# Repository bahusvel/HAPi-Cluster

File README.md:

# ClusterPipe
Flow processing scheduler daemon for real time parallel stream processing

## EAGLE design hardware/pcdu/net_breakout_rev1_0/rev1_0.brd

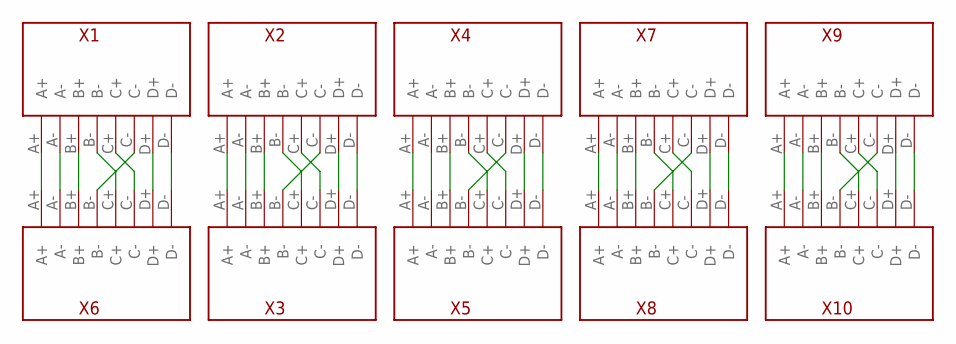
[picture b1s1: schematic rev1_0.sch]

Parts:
X1, X2, X3, X4, X5, X6, X7, X8, X9, X10: ETHER_BRKOUT

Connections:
unnamed: X1.A+, X6.A+
unnamed: X1.A-, X6.A-
unnamed: X1.B+, X6.B+
unnamed: X1.C-, X6.B-
unnamed: X1.B-, X6.C+
unnamed: X1.C+, X6.C-
unnamed: X1.D+, X6.D+
unnamed: X1.D-, X6.D-
unnamed: X2.A+, X3.A+
unnamed: X2.A-, X3.A-
unnamed: X2.B+, X3.B+
unnamed: X2.C-, X3.B-
unnamed: X2.B-, X3.C+
unnamed: X2.C+, X3.C-
unnamed: X2.D+, X3.D+
unnamed: X2.D-, X3.D-
unnamed: X4.A+, X5.A+
unnamed: X4.A-, X5.A-
unnamed: X4.B+, X5.B+
unnamed: X4.C-, X5.B-
unnamed: X4.B-, X5.C+
unnamed: X4.C+, X5.C-
unnamed: X4.D+, X5.D+
unnamed: X4.D-, X5.D-
unnamed: X7.A+, X8.A+
unnamed: X7.A-, X8.A-
unnamed: X7.B+, X8.B+
unnamed: X7.C-, X8.B-
unnamed: X7.B-, X8.C+
unnamed: X7.C+, X8.C-
unnamed: X7.D+, X8.D+
unnamed: X7.D-, X8.D-
unnamed: X9.A+, X10.A+
unnamed: X9.A-, X10.A-
unnamed: X9.B+, X10.B+
unnamed: X9.C-, X10.B-
unnamed: X9.B-, X10.C+
unnamed: X9.C+, X10.C-
unnamed: X9.D+, X10.D+
unnamed: X9.D-, X10.D-

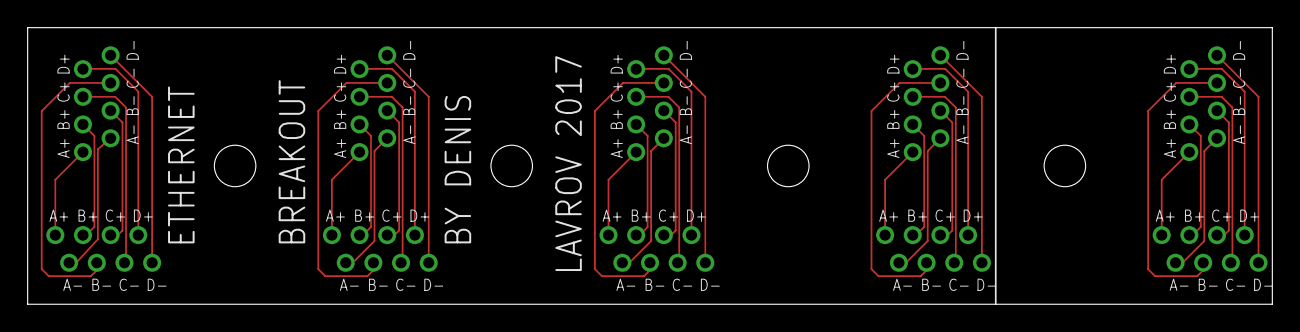
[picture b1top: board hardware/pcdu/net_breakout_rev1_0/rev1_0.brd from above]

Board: 2 copper layers, 90.0 x 20.0 mm, 10 parts (0 on the bottom side), 40 nets.

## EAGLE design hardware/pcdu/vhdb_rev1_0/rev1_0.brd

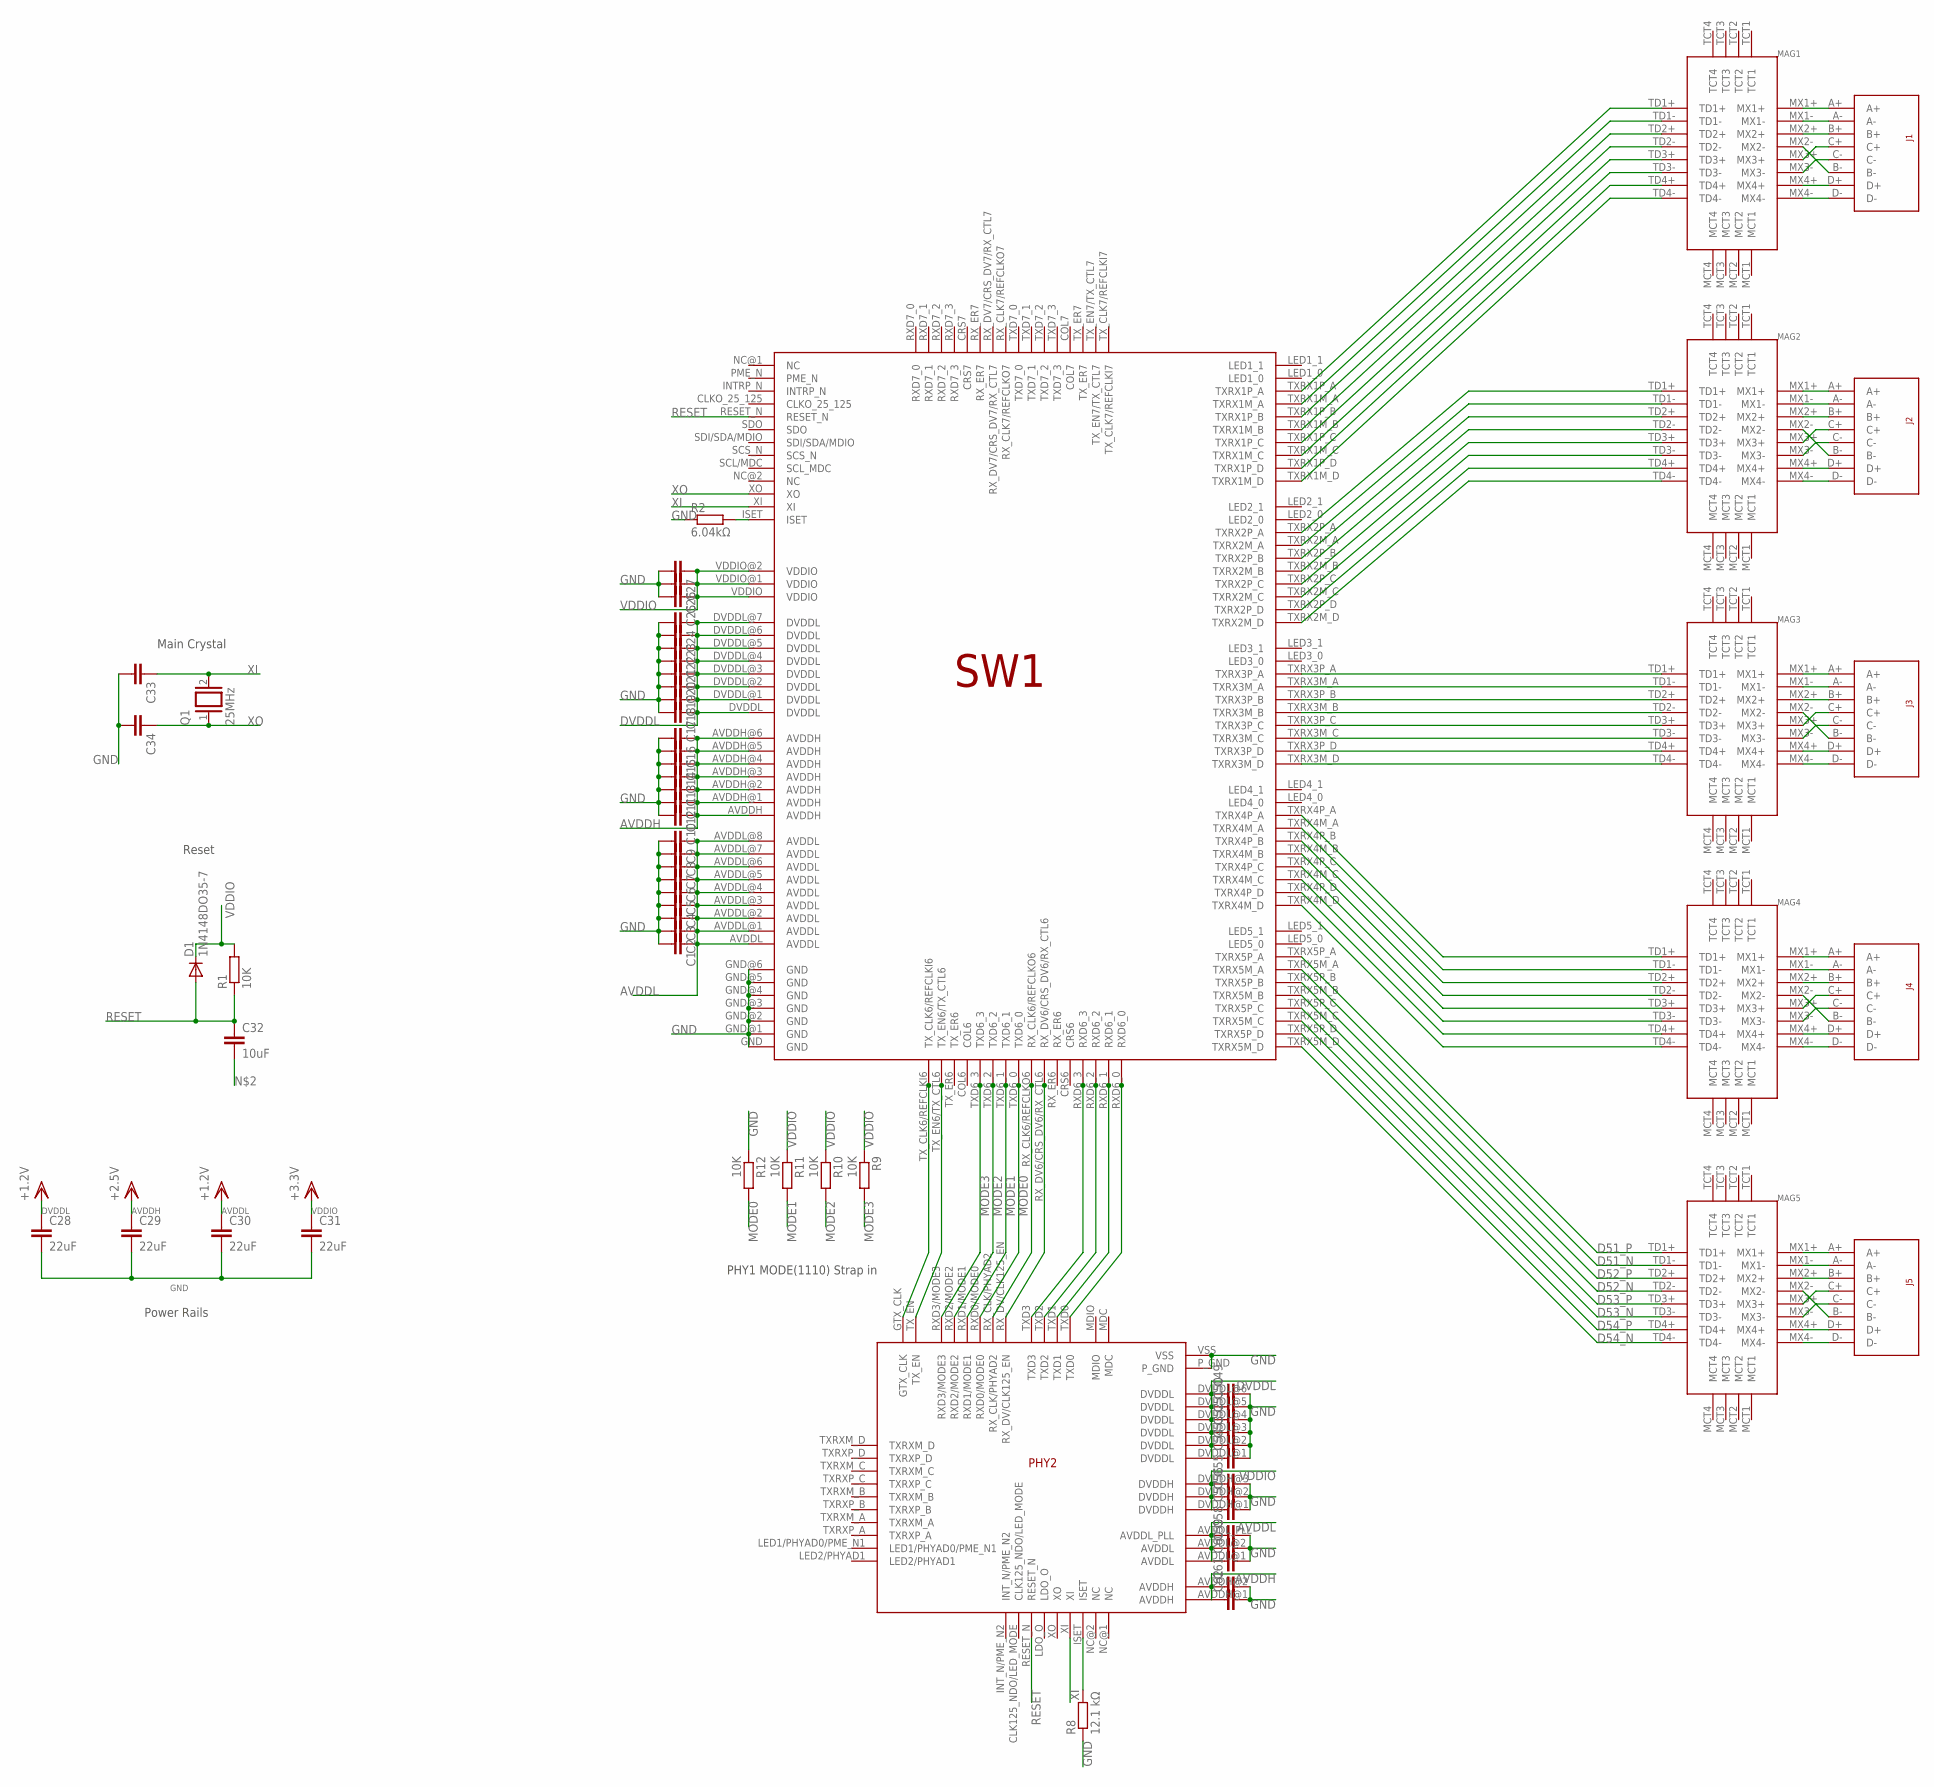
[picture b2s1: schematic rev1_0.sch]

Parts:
C1, C2, C3, C4, C5, C6, C7, C8, C9, C10, C11, C12, C13, C14, C15, C16, C17, C18, C19, C20, C21, C22, C23, C24, C25, C26, C27, C33, C34, C49, C50, C51, C52, C53, C54, C55, C56, C57, C58, C59, C60, C61, C62: C-EUC0805; C0805
C28, C29, C30, C31: 22uF; C0805
C32: 10uF; C0805
D1: 1N4148DO35-7; DO35-7
J1, J2, J3, J4, J5: AJP92A8813
MAG1, MAG2, MAG3, MAG4, MAG5: 749020010A; 749023010A
PHY2: KSZ9031RNX
Q1: 25MHz; QS
R1, R9, R10, R11, R12: 10K; R0805
R2: 6.04kΩ; R0805
R8: 12.1 kΩ; R0805
SW1: KSZ9897RTXC

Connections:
AVDDH: C10.1, C11.1, C12.1, C13.1, C14.1, C15.1, C16.1, C29.1, PHY2.AVDDH@1 (AVDDH), PHY2.AVDDH@2 (AVDDH), SW1.AVDDH, SW1.AVDDH@1 (AVDDH), SW1.AVDDH@2 (AVDDH), SW1.AVDDH@3 (AVDDH), SW1.AVDDH@4 (AVDDH), SW1.AVDDH@5 (AVDDH), SW1.AVDDH@6 (AVDDH)
AVDDL: C1.1, C2.1, C3.1, C4.1, C5.1, C6.1, C7.1, C8.1, C9.1, C30.1, PHY2.AVDDL@1 (AVDDL), PHY2.AVDDL@2 (AVDDL), PHY2.AVDDL_PLL, SW1.AVDDL, SW1.AVDDL@1 (AVDDL), SW1.AVDDL@2 (AVDDL), SW1.AVDDL@3 (AVDDL), SW1.AVDDL@4 (AVDDL), SW1.AVDDL@5 (AVDDL), SW1.AVDDL@6 (AVDDL), SW1.AVDDL@7 (AVDDL), SW1.AVDDL@8 (AVDDL)
D51_N: MAG5.TD1-, SW1.TXRX5M_A
D51_P: MAG5.TD1+, SW1.TXRX5P_A
D52_N: MAG5.TD2-, SW1.TXRX5M_B
D52_P: MAG5.TD2+, SW1.TXRX5P_B
D53_N: MAG5.TD3-, SW1.TXRX5M_C
D53_P: MAG5.TD3+, SW1.TXRX5P_C
D54_N: MAG5.TD4-, SW1.TXRX5M_D
D54_P: MAG5.TD4+, SW1.TXRX5P_D
DVDDL: C17.1, C24.1, C28.1, C49.1, PHY2.DVDDL@1 (DVDDL), PHY2.DVDDL@2 (DVDDL), PHY2.DVDDL@3 (DVDDL), PHY2.DVDDL@4 (DVDDL), PHY2.DVDDL@5 (DVDDL), PHY2.DVDDL@6 (DVDDL), SW1.DVDDL, SW1.DVDDL@1 (DVDDL), SW1.DVDDL@2 (DVDDL), SW1.DVDDL@3 (DVDDL), SW1.DVDDL@4 (DVDDL), SW1.DVDDL@5 (DVDDL), SW1.DVDDL@6 (DVDDL), SW1.DVDDL@7 (DVDDL)
GND: C1.2, C2.2, C3.2, C4.2, C5.2, C6.2, C7.2, C8.2, C9.2, C10.2, C11.2, C12.2, C13.2, C14.2, C15.2, C16.2, C17.2, C18.2, C19.2, C20.2, C21.2, C22.2, C23.2, C24.2, C25.2, C26.2, C27.2, C28.2, C29.2, C30.2, C31.2, C33.2, C34.2, C49.2, C51.2, C52.2, C53.2, C54.2, C55.2, C57.2, C58.2, C60.2, C61.2, C62.2, PHY2.P_GND, PHY2.VSS, R2.1, R8.1, R12.1, SW1.GND, SW1.GND@1 (GND), SW1.GND@2 (GND), SW1.GND@3 (GND), SW1.GND@4 (GND), SW1.GND@5 (GND), SW1.GND@6 (GND)
MODE0: PHY2.RXD0/MODE0, R12.2, SW1.TXD6_0
MODE1: PHY2.RXD1/MODE1, R11.2, SW1.TXD6_1
MODE2: PHY2.RXD2/MODE2, R10.2, SW1.TXD6_2
MODE3: PHY2.RXD3/MODE3, R9.2, SW1.TXD6_3
unnamed: MAG1.TD1+, SW1.TXRX1P_A
unnamed: MAG1.TD1-, SW1.TXRX1M_A
unnamed: MAG1.TD2+, SW1.TXRX1P_B
unnamed: MAG1.TD2-, SW1.TXRX1M_B
unnamed: R2.2, SW1.ISET
unnamed: MAG1.TD3+, SW1.TXRX1P_C
unnamed: MAG1.TD3-, SW1.TXRX1M_C
unnamed: MAG1.TD4+, SW1.TXRX1P_D
unnamed: MAG1.TD4-, SW1.TXRX1M_D
unnamed: MAG2.TD1+, SW1.TXRX2P_A
unnamed: MAG2.TD1-, SW1.TXRX2M_A
unnamed: MAG2.TD2+, SW1.TXRX2P_B
unnamed: MAG2.TD2-, SW1.TXRX2M_B
unnamed: MAG2.TD3+, SW1.TXRX2P_C
unnamed: MAG2.TD3-, SW1.TXRX2M_C
unnamed: MAG2.TD4+, SW1.TXRX2P_D
unnamed: MAG2.TD4-, SW1.TXRX2M_D
unnamed: MAG3.TD1+, SW1.TXRX3P_A
unnamed: MAG3.TD1-, SW1.TXRX3M_A
unnamed: MAG3.TD2+, SW1.TXRX3P_B
unnamed: MAG3.TD2-, SW1.TXRX3M_B
unnamed: MAG3.TD3+, SW1.TXRX3P_C
unnamed: MAG3.TD3-, SW1.TXRX3M_C
unnamed: MAG3.TD4+, SW1.TXRX3P_D
unnamed: MAG3.TD4-, SW1.TXRX3M_D
unnamed: MAG4.TD4-, SW1.TXRX4M_D
unnamed: MAG4.TD4+, SW1.TXRX4P_D
unnamed: MAG4.TD3-, SW1.TXRX4M_C
unnamed: MAG4.TD3+, SW1.TXRX4P_C
unnamed: MAG4.TD2-, SW1.TXRX4M_B
unnamed: MAG4.TD2+, SW1.TXRX4P_B
unnamed: MAG4.TD1-, SW1.TXRX4M_A
unnamed: MAG4.TD1+, SW1.TXRX4P_A
unnamed: J1.A+, MAG1.MX1+
unnamed: J1.A-, MAG1.MX1-
unnamed: J1.B+, MAG1.MX2+
unnamed: J1.B-, MAG1.MX2-
unnamed: J1.C+, MAG1.MX3+
unnamed: J1.C-, MAG1.MX3-
unnamed: J1.D+, MAG1.MX4+
unnamed: J1.D-, MAG1.MX4-
unnamed: J2.A+, MAG2.MX1+
unnamed: J2.A-, MAG2.MX1-
unnamed: J2.B+, MAG2.MX2+
unnamed: J2.B-, MAG2.MX2-
unnamed: J2.C+, MAG2.MX3+
unnamed: J2.C-, MAG2.MX3-
unnamed: J2.D+, MAG2.MX4+
unnamed: J2.D-, MAG2.MX4-
unnamed: J3.A+, MAG3.MX1+
unnamed: J3.A-, MAG3.MX1-
unnamed: J3.B+, MAG3.MX2+
unnamed: J3.B-, MAG3.MX2-
unnamed: J3.C+, MAG3.MX3+
unnamed: J3.C-, MAG3.MX3-
unnamed: J3.D+, MAG3.MX4+
unnamed: J3.D-, MAG3.MX4-
unnamed: J4.A+, MAG4.MX1+
unnamed: J4.A-, MAG4.MX1-
unnamed: J4.B+, MAG4.MX2+
unnamed: J4.B-, MAG4.MX2-
unnamed: J4.C+, MAG4.MX3+
unnamed: J4.C-, MAG4.MX3-
unnamed: J4.D+, MAG4.MX4+
unnamed: J4.D-, MAG4.MX4-
unnamed: J5.A+, MAG5.MX1+
unnamed: J5.A-, MAG5.MX1-
unnamed: J5.B+, MAG5.MX2+
unnamed: J5.B-, MAG5.MX2-
unnamed: J5.C+, MAG5.MX3+
unnamed: J5.C-, MAG5.MX3-
unnamed: J5.D+, MAG5.MX4+
unnamed: J5.D-, MAG5.MX4-
unnamed: PHY2.TXD0, SW1.RXD6_0
unnamed: PHY2.TXD1, SW1.RXD6_1
unnamed: PHY2.TXD2, SW1.RXD6_2
unnamed: PHY2.TXD3, SW1.RXD6_3
unnamed: PHY2.RX_DV/CLK125_EN, SW1.RX_DV6/CRS_DV6/RX_C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
unnamed: PHY2.RX_CLK/PHYAD2, SW1.RX_CLK6/REFCLKO6
unnamed: PHY2.TX_EN, SW1.TX_EN6/TX_CTL6
unnamed: PHY2.GTX_CLK, SW1.TX_CLK6/REFCLKI6
unnamed: PHY2.ISET, R8.2
RESET: C32.1, D1.A, PHY2.RESET_N, R1.1, SW1.RESET_N
VDDIO: C25.1, C26.1, C27.1, C31.1, D1.C, PHY2.DVDDH@1 (DVDDH), PHY2.DVDDH@2 (DVDDH), PHY2.DVDDH@3 (DVDDH), R1.2, R9.1, R10.1, R11.1, SW1.VDDIO, SW1.VDDIO@1 (VDDIO), SW1.VDDIO@2 (VDDIO)
XI: C33.1, PHY2.XI, Q1.2, SW1.XI
XO: C34.1, Q1.1, SW1.XO

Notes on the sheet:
Main Crystal
Reset
Power Rails
PHY1 MODE(1110) Strap in

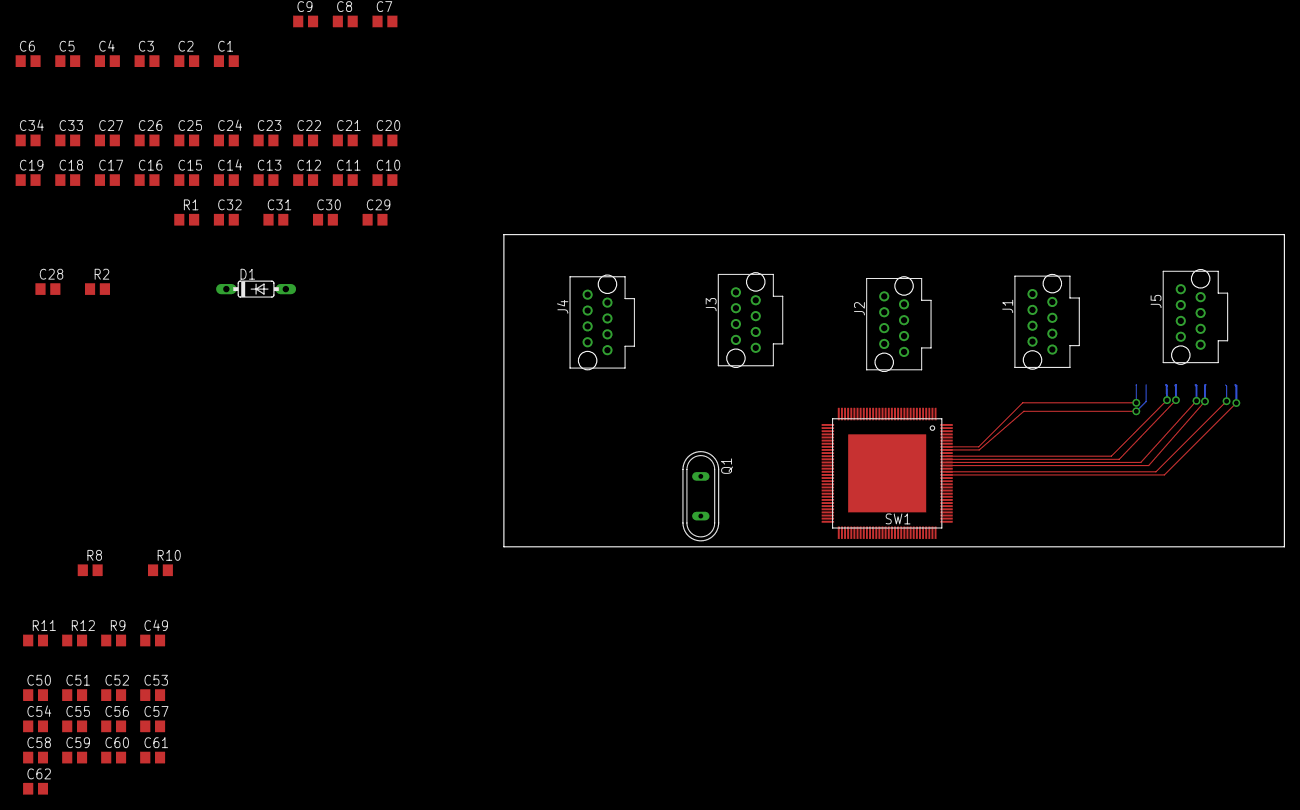
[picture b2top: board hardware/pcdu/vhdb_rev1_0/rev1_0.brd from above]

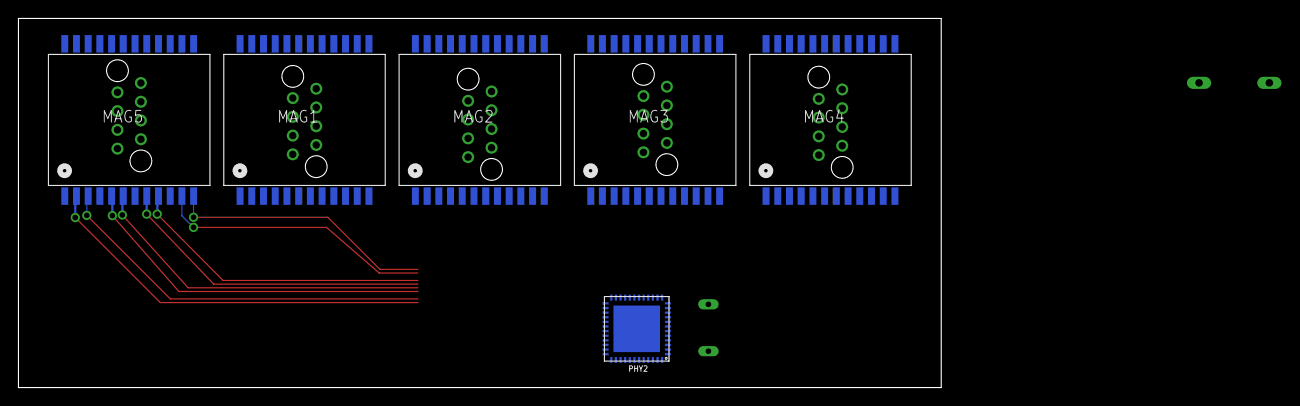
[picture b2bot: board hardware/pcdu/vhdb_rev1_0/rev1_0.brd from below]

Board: 2 copper layers, 100.0 x 40.0 mm, 69 parts (6 on the bottom side), 102 nets.

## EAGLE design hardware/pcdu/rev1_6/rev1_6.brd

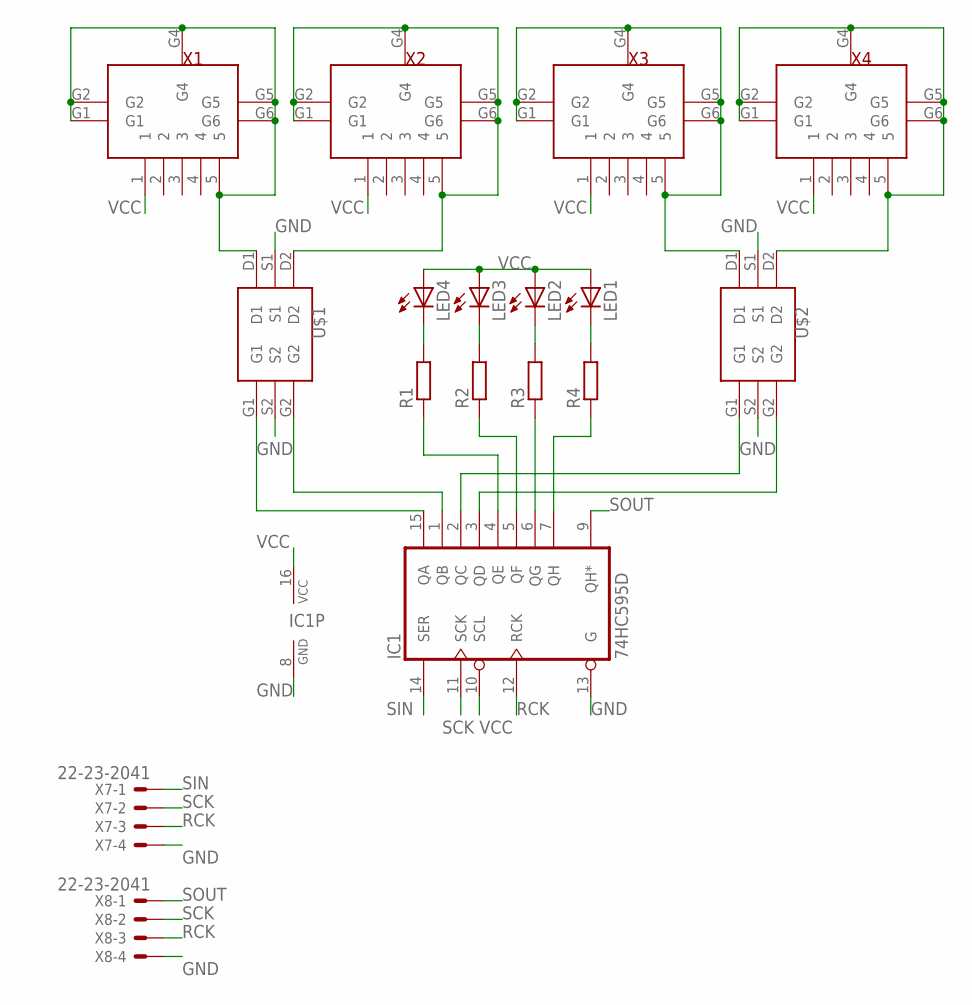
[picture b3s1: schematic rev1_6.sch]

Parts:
IC1: 74HC595D; SO16
LED1, LED2, LED3, LED4: LED_E; LED_1206
R1, R2, R3, R4: RR1005; R1005
U$1, U$2: FDC6305N; FDC6305
X1, X2, X3, X4: MUSBV
X7, X8: 22-23-2041

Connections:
GND: IC1.8 (GND), IC1.13 (G), U$1.S1, U$1.S2, U$2.S1, U$2.S2, X7.4, X8.4
unnamed: IC1.15 (QA), U$1.G1
unnamed: IC1.1 (QB), U$1.G2
unnamed: IC1.2 (QC), U$2.G1
unnamed: IC1.3 (QD), U$2.G2
unnamed: LED4.C, R1.2
unnamed: LED3.C, R2.2
unnamed: LED2.C, R3.2
unnamed: LED1.C, R4.2
unnamed: U$1.D1, X1.5, X1.G1, X1.G2, X1.G4, X1.G5, X1.G6
unnamed: U$1.D2, X2.5, X2.G1, X2.G2, X2.G4, X2.G5, X2.G6
unnamed: U$2.D1, X3.5, X3.G1, X3.G2, X3.G4, X3.G5, X3.G6
unnamed: U$2.D2, X4.5, X4.G1, X4.G2, X4.G4, X4.G5, X4.G6
unnamed: IC1.4 (QE), R1.1
unnamed: IC1.5 (QF), R2.1
unnamed: IC1.6 (QG), R3.1
unnamed: IC1.7 (QH), R4.1
RCK: IC1.12 (RCK), X7.3, X8.3
SCK: IC1.11 (SCK), X7.2, X8.2
SIN: IC1.14 (SER), X7.1
SOUT: IC1.9 (QH*), X8.1
VCC: IC1.10 (SCL), IC1.16 (VCC), LED1.A, LED2.A, LED3.A, LED4.A, X1.1, X2.1, X3.1, X4.1

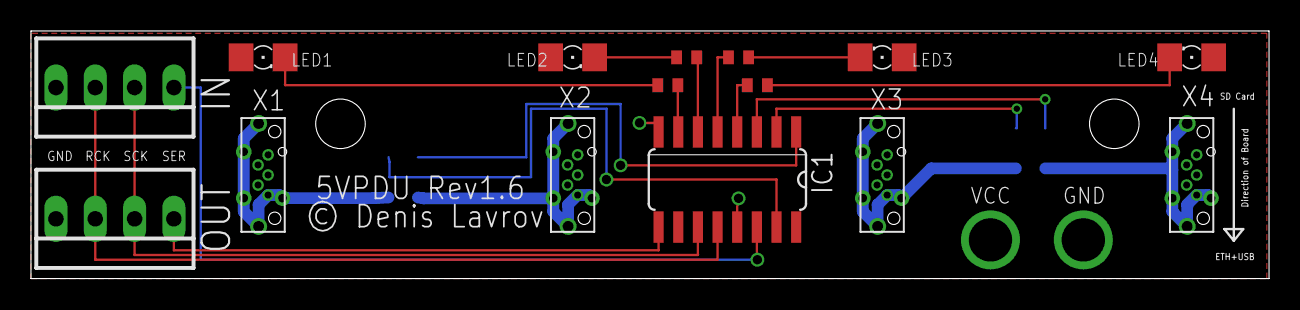
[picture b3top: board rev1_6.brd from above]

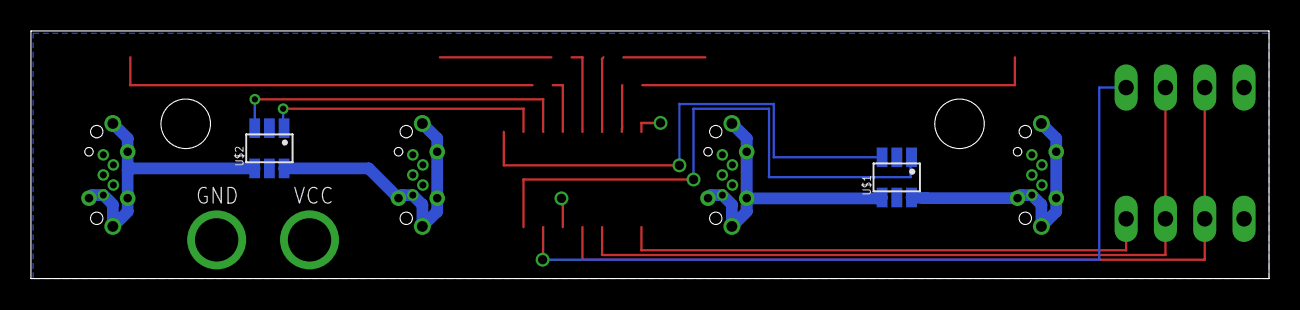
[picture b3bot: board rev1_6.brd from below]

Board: 2 copper layers, 80.0 x 16.0 mm, 17 parts (2 on the bottom side), 22 nets.

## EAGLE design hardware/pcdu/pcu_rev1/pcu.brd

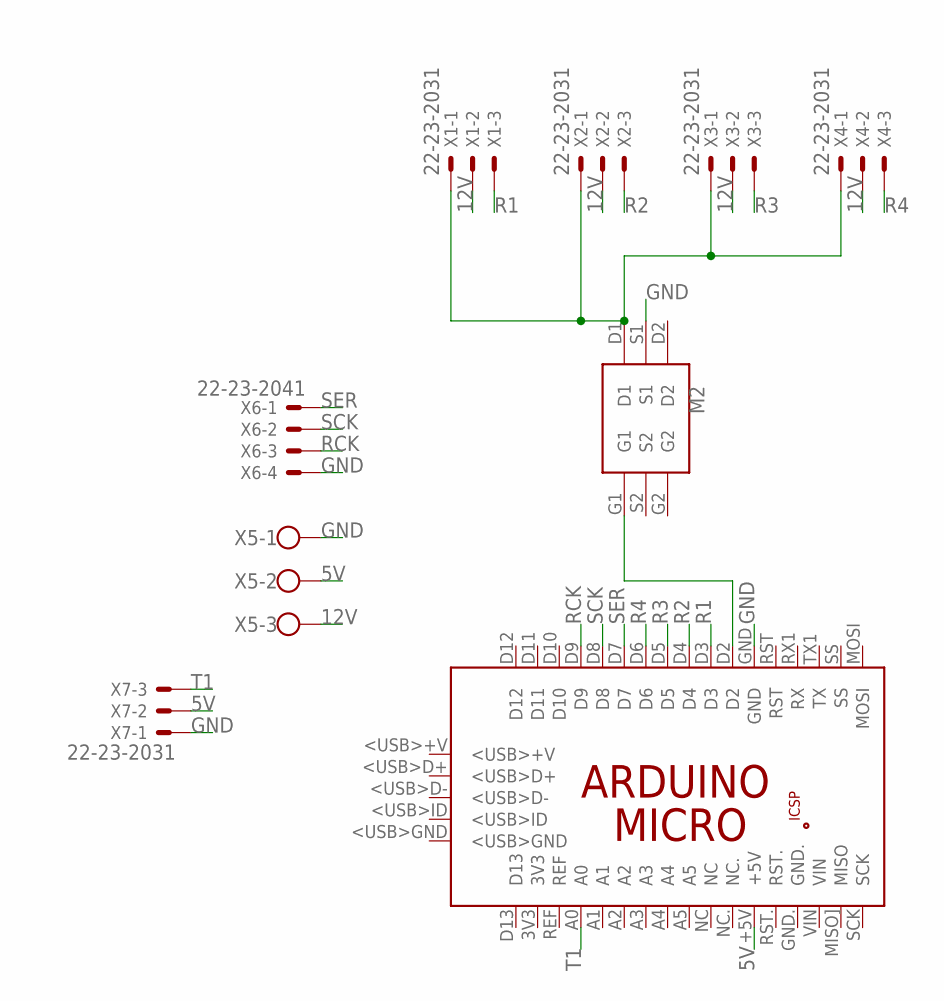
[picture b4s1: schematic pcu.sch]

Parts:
M2: FDC6305N; FDC6305
PCB1: ARDUINO_MICRO
X1, X2, X3, X4, X7: 22-23-2031
X5: W237-103
X6: 22-23-2041

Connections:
5V: PCB1.+5V, X5.2, X7.2
12V: X1.2, X2.2, X3.2, X4.2, X5.3
GND: M2.S1, PCB1.GND, X5.1, X6.4, X7.1
unnamed: M2.D1, X1.1, X2.1, X3.1, X4.1
unnamed: M2.G1, PCB1.D2
R1: PCB1.D3, X1.3
R2: PCB1.D4, X2.3
R3: PCB1.D5, X3.3
R4: PCB1.D6, X4.3
RCK: PCB1.D9, X6.3
SCK: PCB1.D8, X6.2
SER: PCB1.D7, X6.1
T1: PCB1.A0, X7.3

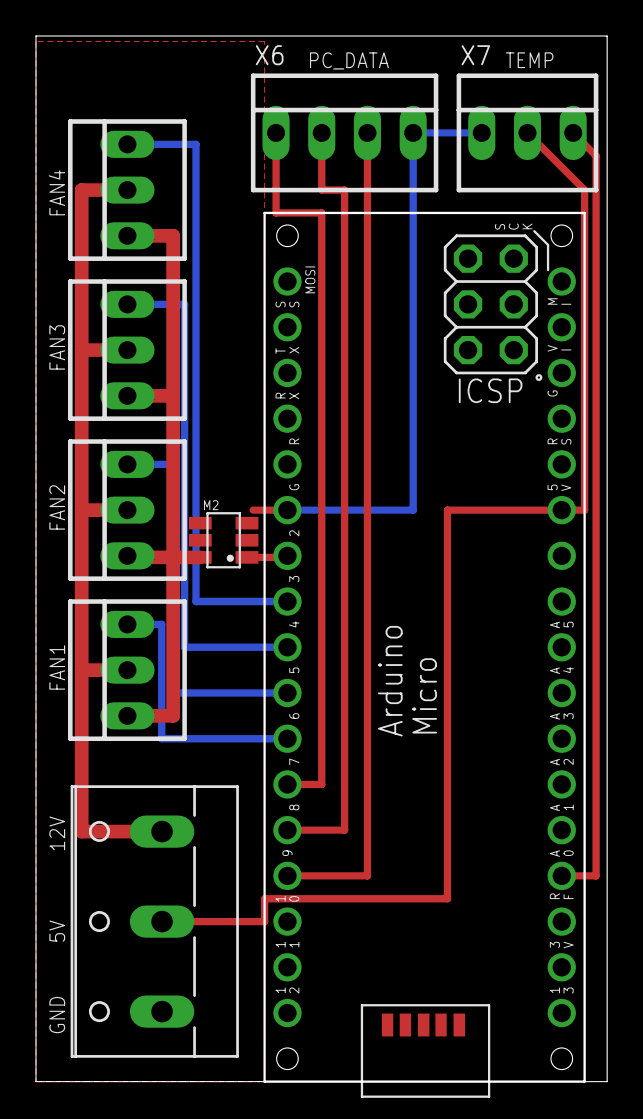
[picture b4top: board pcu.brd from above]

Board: 2 copper layers, 31.7 x 58.1 mm, 9 parts (0 on the bottom side), 13 nets.

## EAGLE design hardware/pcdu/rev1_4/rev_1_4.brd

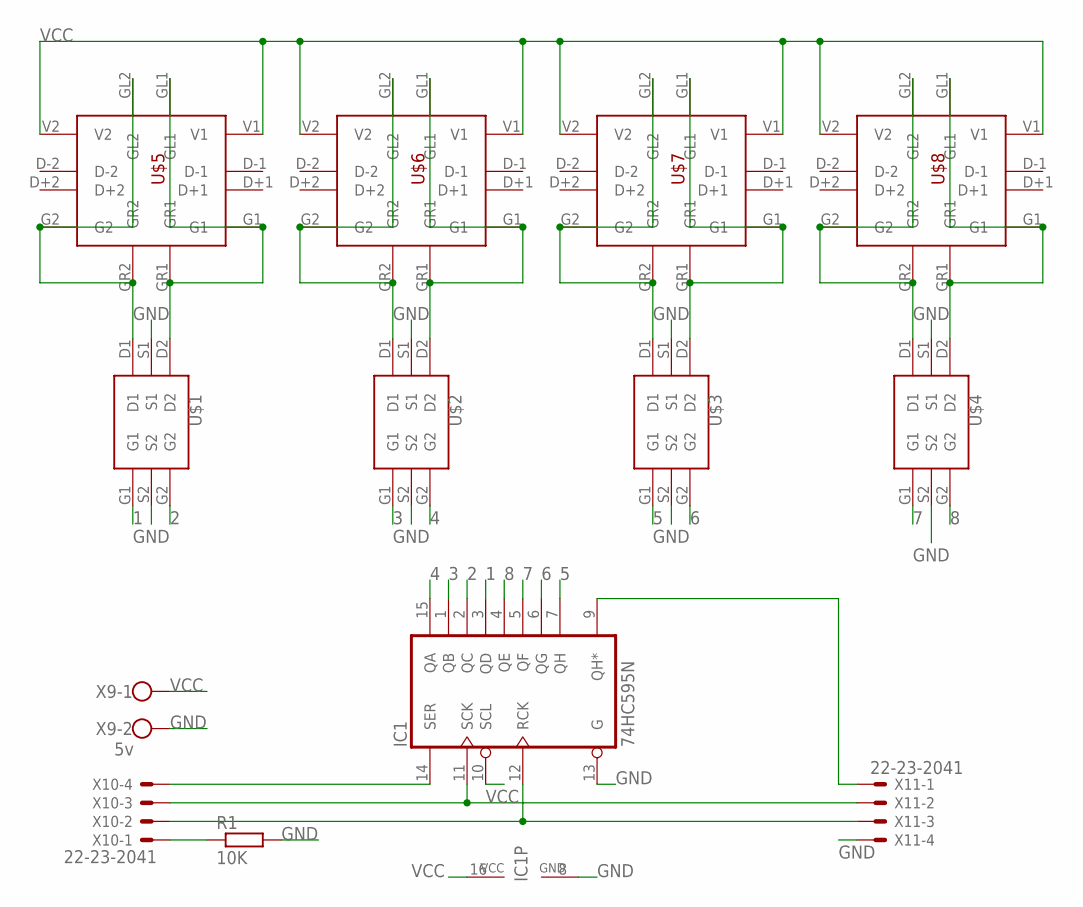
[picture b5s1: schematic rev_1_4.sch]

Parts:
IC1: 74HC595N; DIL16
R1: 10K; 0204/7
U$1, U$2, U$3, U$4: FDC6305N; FDC6305
U$5, U$6, U$7, U$8: USB2V
X9: 5v; W237-102
X10, X11: 22-23-2041

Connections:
1: IC1.3 (QD), U$1.G1
2: IC1.2 (QC), U$1.G2
3: IC1.1 (QB), U$2.G1
4: IC1.15 (QA), U$2.G2
5: IC1.7 (QH), U$3.G1
6: IC1.6 (QG), U$3.G2
7: IC1.5 (QF), U$4.G1
8: IC1.4 (QE), U$4.G2
GND: IC1.8 (GND), IC1.13 (G), R1.2, U$1.S1, U$1.S2, U$2.S1, U$2.S2, U$3.S1, U$3.S2, U$4.S1, U$4.S2, X9.2, X11.4
unnamed: U$1.D1, U$5.G2, U$5.GL2, U$5.GR2
unnamed: U$1.D2, U$5.G1, U$5.GL1, U$5.GR1
unnamed: U$2.D1, U$6.G2, U$6.GL2, U$6.GR2
unnamed: U$2.D2, U$6.G1, U$6.GL1, U$6.GR1
unnamed: U$3.D1, U$7.G2, U$7.GL2, U$7.GR2
unnamed: U$3.D2, U$7.G1, U$7.GL1, U$7.GR1
unnamed: U$4.D1, U$8.G2, U$8.GL2, U$8.GR2
unnamed: U$4.D2, U$8.G1, U$8.GL1, U$8.GR1
unnamed: R1.1, X10.1
unnamed: IC1.9 (QH*), X11.1
unnamed: IC1.14 (SER), X10.4
unnamed: IC1.11 (SCK), X10.3, X11.2
unnamed: IC1.12 (RCK), X10.2, X11.3
VCC: IC1.10 (SCL), IC1.16 (VCC), U$5.V1, U$5.V2, U$6.V1, U$6.V2, U$7.V1, U$7.V2, U$8.V1, U$8.V2, X9.1

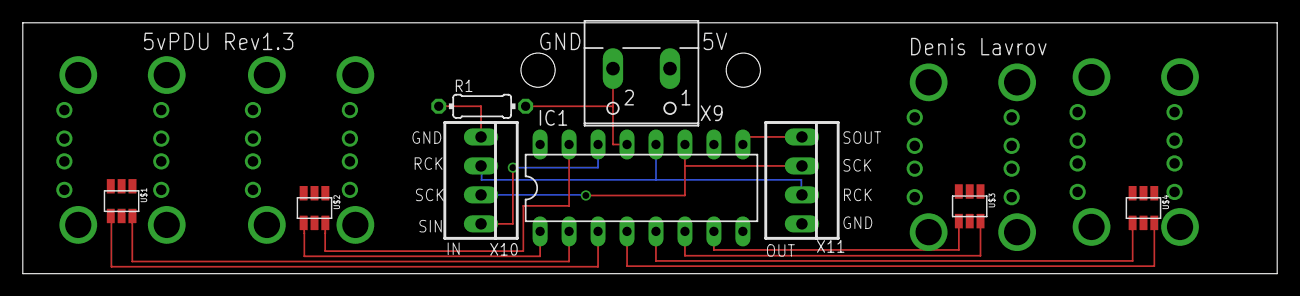
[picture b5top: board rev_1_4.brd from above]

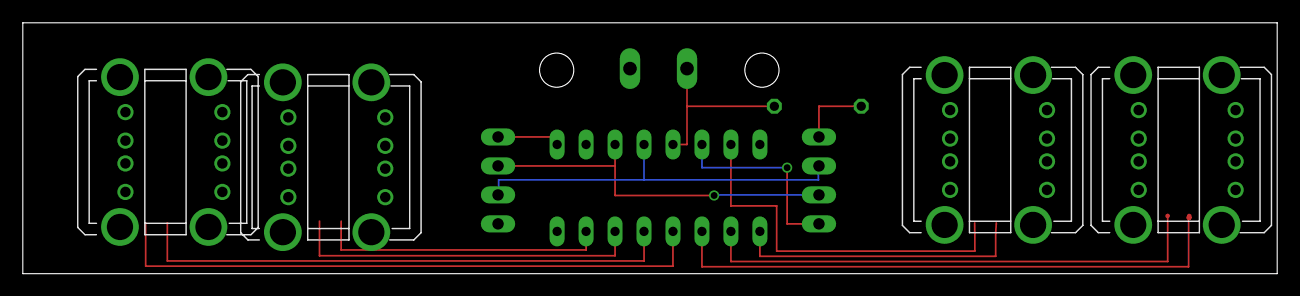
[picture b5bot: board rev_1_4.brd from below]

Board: 2 copper layers, 110.0 x 22.0 mm, 13 parts (4 on the bottom side), 23 nets.

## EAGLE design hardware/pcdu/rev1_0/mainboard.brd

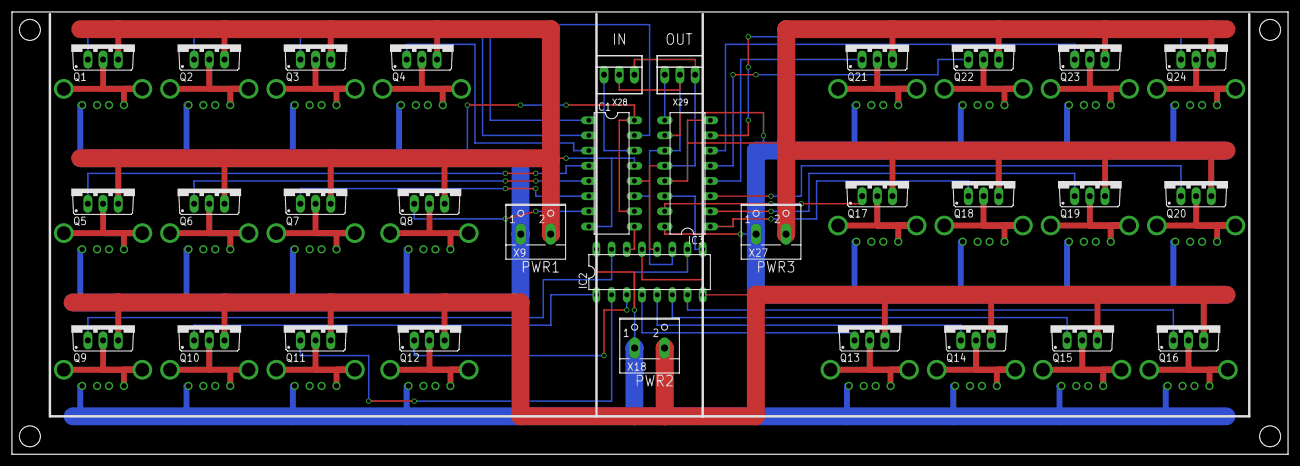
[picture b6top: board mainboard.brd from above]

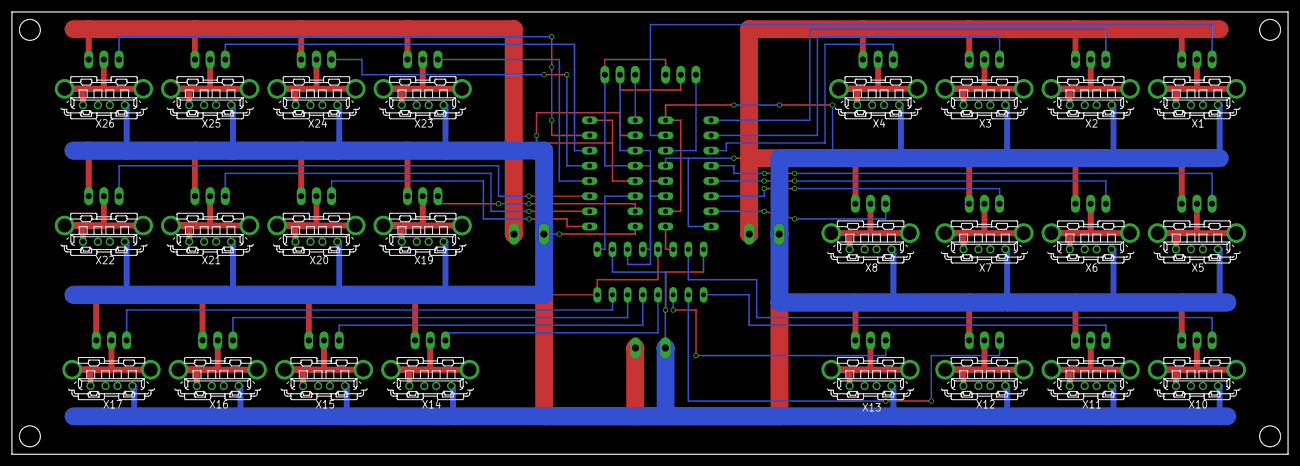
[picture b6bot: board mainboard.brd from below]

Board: 2 copper layers, 213.5 x 74.0 mm, 56 parts (24 on the bottom side), 60 nets.

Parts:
IC1, IC2, IC3: 74HC595N; DIL16
Q1, Q2, Q3, Q4, Q5, Q6, Q7, Q8, Q9, Q10, Q11, Q12, Q13, Q14, Q15, Q16, Q17, Q18, Q19, Q20, Q21, Q22, Q23, Q24: IRF540; TO220BV
X1, X2, X3, X4, X5, X6, X7, X8, X10, X11, X12, X13, X14, X15, X16, X17, X19, X20, X21, X22, X23, X24, X25, X26: KUSBVX
X9, X18, X27: 5v; W237-102
X28, X29: 22-23-2031

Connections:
B$1: IC2.8, IC2.13, Q9.S, Q10.S, Q11.S, Q12.S, Q13.S, Q14.S, Q15.S, Q16.S, X18.2
B$2: IC1.8, IC1.13, Q1.S, Q2.S, Q3.S, Q4.S, Q5.S, Q6.S, Q7.S, Q8.S, X9.2
B$3: IC3.8, IC3.13, Q17.S, Q18.S, Q19.S, Q20.S, Q21.S, Q22.S, Q23.S, Q24.S, X27.2
unnamed: IC1.15, Q1.G
unnamed: IC1.1, Q2.G
unnamed: IC1.2, Q3.G
unnamed: IC1.3, Q4.G
unnamed: IC1.4, Q5.G
unnamed: IC1.5, Q6.G
unnamed: IC1.7, Q8.G
unnamed: IC1.6, Q7.G
unnamed: Q1.D, X1.4, X1.M1, X1.M2
unnamed: Q11.D, X12.4, X12.M1, X12.M2
unnamed: Q3.D, X3.4, X3.M1, X3.M2
unnamed: Q4.D, X4.4, X4.M1, X4.M2
unnamed: Q5.D, X5.4, X5.M1, X5.M2
unnamed: IC1.10, IC1.16, X1.1, X2.1, X3.1, X4.1, X5.1, X6.1, X7.1, X8.1, X9.1
unnamed: Q7.D, X7.4, X7.M1, X7.M2
unnamed: Q16.D, X17.4, X17.M1, X17.M2
unnamed: Q2.D, X2.4, X2.M1, X2.M2
unnamed: Q12.D, X13.4, X13.M1, X13.M2
unnamed: Q6.D, X6.4, X6.M1, X6.M2
unnamed: Q13.D, X14.4, X14.M1, X14.M2
unnamed: Q15.D, X16.4, X16.M1, X16.M2
unnamed: Q14.D, X15.4, X15.M1, X15.M2
unnamed: IC2.10, IC2.16, X10.1, X11.1, X12.1, X13.1, X14.1, X15.1, X16.1, X17.1, X18.1
unnamed: IC1.9, IC2.14
unnamed: Q9.D, X10.4, X10.M1, X10.M2
unnamed: Q10.D, X11.4, X11.M1, X11.M2
unnamed: IC2.15, Q9.G
unnamed: IC2.1, Q10.G
unnamed: IC2.2, Q11.G
unnamed: IC2.3, Q12.G
unnamed: IC2.7, Q16.G
unnamed: IC2.4, Q13.G
unnamed: IC2.5, Q14.G
unnamed: IC2.6, Q15.G
unnamed: IC2.9, IC3.14
unnamed: IC3.9, X29.1
unnamed: Q19.D, X21.4, X21.M1, X21.M2
unnamed: Q20.D, X22.4, X22.M1, X22.M2
unnamed: Q21.D, X23.4, X23.M1, X23.M2
unnamed: Q23.D, X25.4, X25.M1, X25.M2
unnamed: Q22.D, X24.4, X24.M1, X24.M2
unnamed: IC3.10, IC3.16, X19.1, X20.1, X21.1, X22.1, X23.1, X24.1, X25.1, X26.1, X27.1
unnamed: Q8.D, X8.4, X8.M1, X8.M2
unnamed: Q17.D, X19.4, X19.M1, X19.M2
unnamed: Q18.D, X20.4, X20.M1, X20.M2
unnamed: IC3.15, Q17.G
unnamed: IC3.1, Q18.G
unnamed: IC3.2, Q19.G
unnamed: IC3.3, Q20.G
unnamed: IC3.7, Q24.G
unnamed: IC3.4, Q21.G
unnamed: IC3.5, Q22.G
unnamed: IC1.14, X28.1
unnamed: IC3.6, Q23.G
unnamed: Q24.D, X26.4, X26.M1, X26.M2
unnamed: IC1.12, IC2.12, IC3.12, X28.3, X29.3
unnamed: IC1.11, IC2.11, IC3.11, X28.2, X29.2

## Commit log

2016-11-30 Added remote pipes
2016-11-30 Organized project, added example job file
2016-11-30 Added http servers, imported code, common code
2016-11-30 Made the compilation through makefile
2016-11-30 Flexible CPCD platform
2016-11-30 Added fifo logic and task scheduler
2016-12-01 Using new rpc, netpipe restructure
2016-12-01 Work on CPCD
2016-12-01 Added general host stat gathering
2016-12-01 Added node status printing
2016-12-03 Writing my own RPC
2016-12-03 RPC seems to be working
2016-12-03 Allow address setting
2016-12-07 Kissrpc updates (auto register server side)
2016-12-07 Added startup code for CPD
2016-12-07 Fixed weird indirection bug
2016-12-07 Fixed comms, successful status reports
2016-12-07 Added initial influxdb integration code
2016-12-08 Getting it to run on real cluster
2016-12-08 Fixed TraverseParamTree
2016-12-08 Influx is working
2016-12-08 Added Scripts
2016-12-08 Added basic scheduling
2016-12-09 Added stat monitoring for controller + disk
2016-12-09 Fixed DiskStat ordering
2016-12-11 Added binary size reduction
2016-12-12 Task scheduling pivot
2016-12-12 Added basic scheduler code
2016-12-13 better cpd distribute
2016-12-13 Finished TCP pipes implementation
2016-12-13 Added script to get ip address
2016-12-13 cpctl should be able to schedule now
2016-12-17 Added service mode
2016-12-18 Added pcu code, and chassis controller
2016-12-18 Enabled compiler warnings
2016-12-22 Added tftp boot server
2016-12-28 PCU fully functional
2017-01-03 Added mapping between logical units and physical ports
2017-01-16 Moved software, added FDC6305N Libary, added rev 1
2017-01-16 Removed incorrect files, added renders
2017-01-17 Merged ClusterPipe with HAPi-Cluster
2017-01-17 Uploaded Stage1 BOM
2017-01-17 Added Stage2 purchase list
2017-01-18 Started work on rev1_4 board
2017-01-18 Removed eagle trash
2017-01-18 Local power distribution board design
2017-01-19 Added boot controller
2017-01-19 Added ip auto configuration
2017-01-19 Added cpd.service config
2017-01-21 Added PCU board, updated revision 5 PDU board
2017-01-21 Added dru file for the board house of choice
2017-01-21 Added an early in rack render
2017-01-22 Updated parts list
2017-01-23 Added another render, modifications to pcu firmware
2017-01-23 Added software controlled LED indicators to rev1_5
2017-01-25 Added a unit lid, updated to solidworks 2017
2017-01-28 Updated PDU board, removed screw terminal
2017-01-29 Shrunk width down in preparation for rails
2017-01-29 Fixed power lid, added preliminary rails
2017-01-30 Added interference hole based unit mounting
2017-01-30 Added new mounting desing for RPi
2017-02-01 Moved the power separator further back
2017-02-01 Migrating some parts to 4mm
2017-02-01 Switched relevant parts to 4mm thickness
2017-02-01 Added some maintenance code to allow cpd to register better
2017-02-01 Added grafana vizualization dashboard
2017-02-02 Added some components to stage 2 list
2017-02-03 Added corner braces, starter work on rails
2017-02-04 Finished simplified rail design
2017-02-06 Added STL files for CubePro Trials
2017-02-06 Added preliminary drawings for laser cutting
2017-02-08 Updated 4mm parts to 4.5mm
2017-02-08 Fixed weak sidewall to bottom connection
2017-02-09 Rail work + corner holes
2017-02-09 Strengthening round
2017-02-09 More strenghtening
2017-02-09 Experiencing solidworks corruption
2017-02-10 Added rail latch
2017-02-10 Added endstop, fixed wrong rib height
2017-02-11 Added back grill, fixed handles
2017-02-11 Extended unit to 550, updated the laser cut batches
2017-02-11 Started work on eagle library for switch
2017-02-11 Finished switch IC library, started work on vhdb
2017-02-17 Restructured Switch IC symbol, added male rj45 connector library
2017-02-18 Added PHY to vhdb uplink
2017-02-19 Added lan transformers
2017-02-19 Minor changes to high density board
2017-03-06 Added first iteration pdf laser cut files
2017-03-06 Simplified the fan grill
2017-03-10 Added the ether breakout board

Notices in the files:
hardware/pcdu/rev1_6/rev1_6.brd:
© Denis Lavrov
